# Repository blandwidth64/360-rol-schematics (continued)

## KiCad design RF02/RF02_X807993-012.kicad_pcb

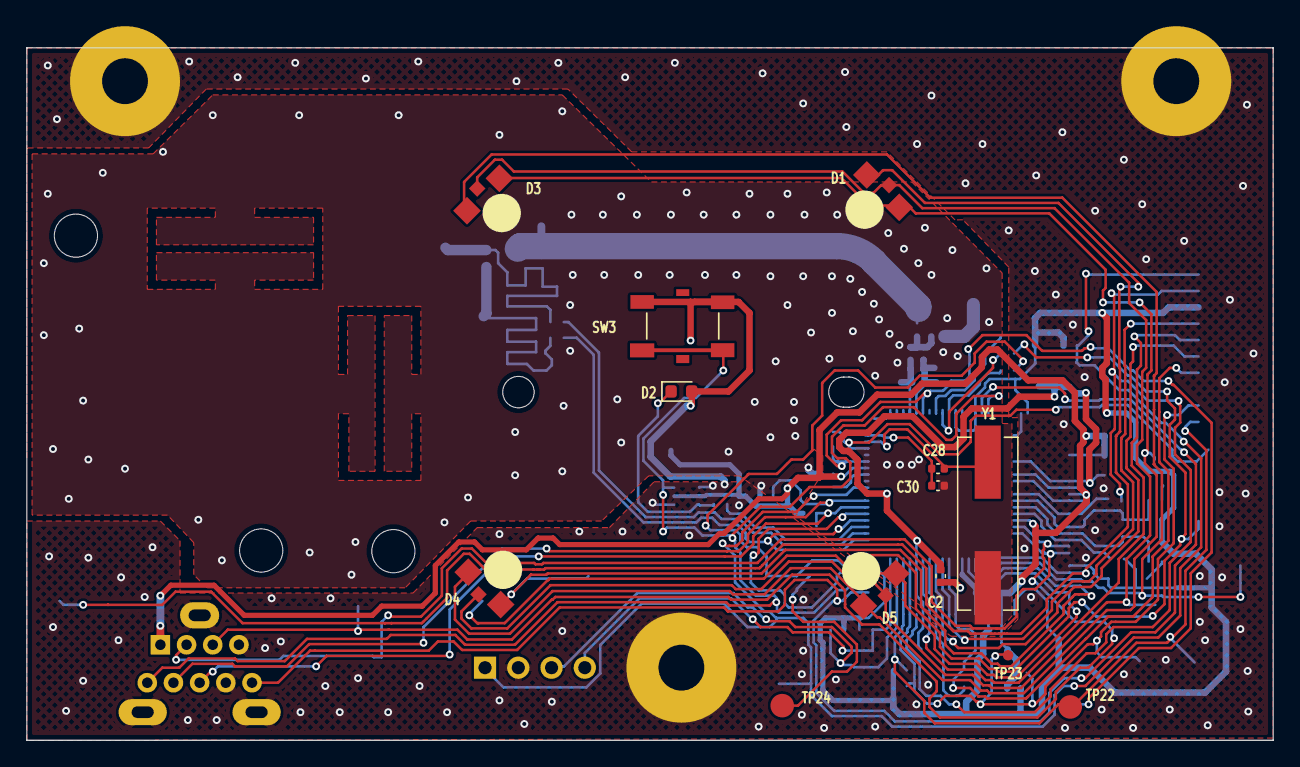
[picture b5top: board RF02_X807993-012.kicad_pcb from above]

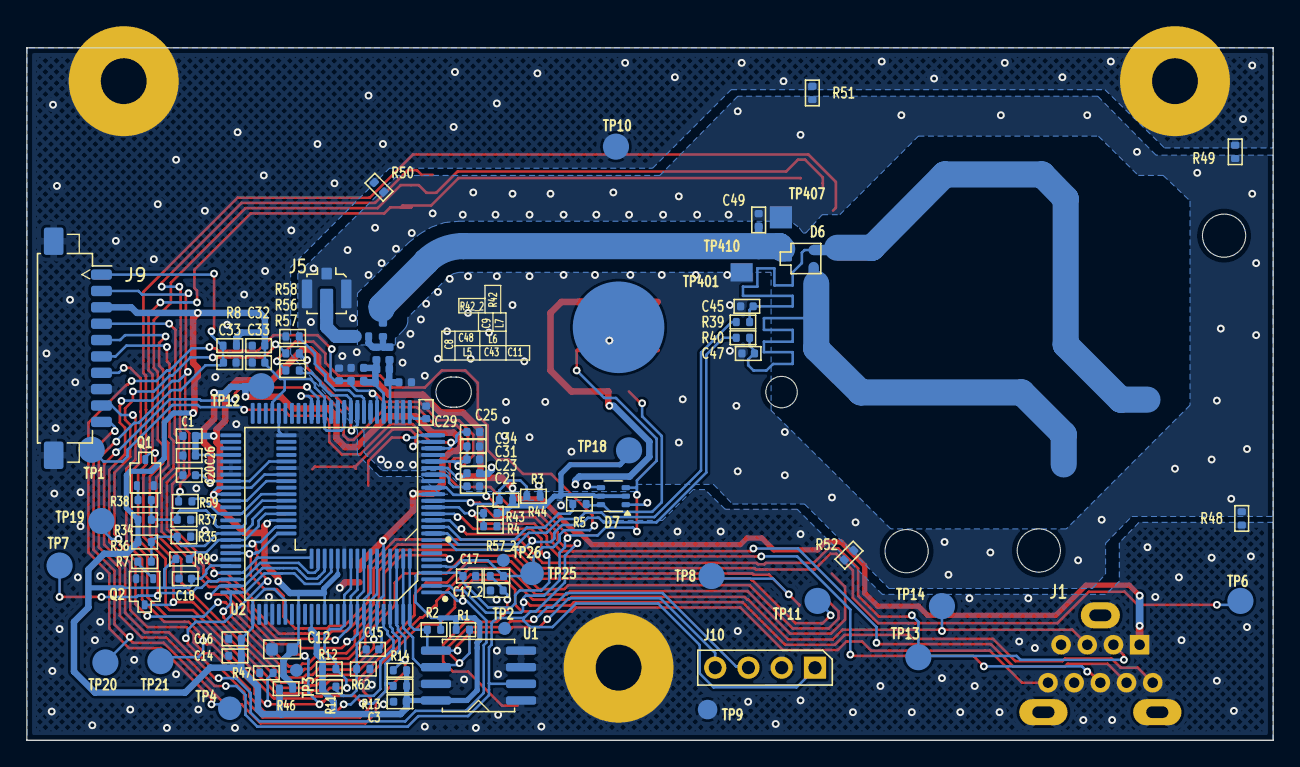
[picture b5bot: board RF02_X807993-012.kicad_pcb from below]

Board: 2 copper layers, 95.2 x 52.9 mm, 115 parts (100 on the bottom side), 58 nets.

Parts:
A1: Argon_ANT
C1, C3, C8, C14, C15, C16, C17, C17_2, C18, C20, C21, C23, C25, C26, C29, C31, C32, C33, C33#2, C34: 0.1 UF; C_0402_1005Metric
C2, C9, C28, C30: C_0402_1005Metric
C11, C43, C48: ~2 PF; C_0402_1005Metric
C12: 0.33 UF; C_0603_1608Metric
C45, C47: ~6.2 PF; C_0402_1005Metric
C49: NC; C_0402_1005Metric
D1, D3, D4, D5: LED_LiteOn_LTST-S326
D2: LED_0603_1608Metric
D6: SOT-323_SC-70
D7: SOT-363_SC-70-6
J1: Argon_Conn
J5: U.FL_Molex_MCRF_73412-0110_Vertical
J9: Molex_PicoBlade_53261-1071_1x10-1MP_P1.25mm_Horiz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; Molex_PicoBlade_53261-1071_1x10-1MP_P1.25mm_Horizontal
J10: PinHeader_1x04_P2.54mm_Vertical
L5, L6, L7: L_0402_1005Metric
Q1, Q2: SOT-323_SC-70
R1, R2: 1.5 KOHM; R_0402_1005Metric
R3, R4, R9, R11, R34, R36, R43, R44, R47, R48, R49, R50, R51, R52, R57_2: NC; R_0402_1005Metric
R5: 220 OHM; R_0402_1005Metric
R7, R38: 1 KOHM; R_0402_1005Metric
R8, R42, R42_2: 47 KOHM; R_0402_1005Metric
R12, R13, R14, R35, R37, R46, R62: 10 KOHM; R_0402_1005Metric
R39, R40: 390 OHM; R_0402_1005Metric
R56, R57, R58, R59: 0 OHM; R_0402_1005Metric
SW3: SW_Push_1P1T_XKB_TS-1187A
TP1, TP2, TP3, TP4, TP6, TP7, TP8, TP9, TP10, TP11, TP12, TP13, TP14, TP18, TP19, TP20, TP21, TP22, TP23, TP24, TP25, TP26, TP410: TestPoint_Pad_D2.0mm
TP35: TestPoint_Pad_D3.0mm
TP401, TP407: TestPoint_Pad_2.0x2.0mm
U1: SOIC-8_5.3x5.3mm_P1.27mm
U2: LQFP-64_10x10mm_P0.5mm
U2_2: LQFP-100_14x14mm_P0.5mm
Y1: Crystal_SMD_HC49-SD

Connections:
ANT_01: A1.1, C45.1, D6.2, R39.2
ANT_01_MATCHING: R39.1, U2.1, U2_2.10
ANT_02: A1.2, C47.1, D6.1, R40.2
ANT_02_MATCHING: R40.1, U2.3, U2_2.9, U2_2.12
ANT_C: C9.1, C43.1, C48.1, L5.2, L6.1, U2.21, U2_2.30
ANT_COAX: J5.1, R42_2.2
ANT_L: C11.1, C43.2, L6.2, L7.1, U2.20, U2_2.29
ANT_MAIN: C49.1, D6.3, R42.1, TP410.1
ANT_R: C9.2, L7.2, R42.2, R42_2.1
C_CLK: J1.C_CLK, R4.1, R43.2, U2.5, U2_2.14
C_DATA: J1.6, R3.1, R44.2, U2.6, U2_2.15
C_NTX: J1.9, U2.31, U2_2.1, U2_2.40
GND: C1.2, C2.1, C3.2, C12.2, C14.2, C15.2, C16.2, C17.2, C17_2.2, C18.2, C20.2, C23.2, C26.2, C32.2, C33.2, C33#2.2, D2.2, D7.1, D7.4, J1.4, J1.8, J1.MP, J9.8, J9.MP, J10.2, Q1.2, Q2.2, R3.2, R4.2, R35.2, R37.2, R47.2, R48.2, R49.2, R50.2, R51.2, R52.2, R58.2, R62.2, SW3.2, TP9.1, TP10.1, TP35.1, U1.1, U1.3, U1.4, U1.7, U2.9, U2.33, U2.38, U2.54, U2_2.18, U2_2.46, U2_2.55, U2_2.56, U2_2.57, U2_2.70, U2_2.78, U2_2.79
GND_0R: R58.1, U2.24, U2_2.33
HEADER_02: J9.2, R59.2, U2_2.96
HEADER_02_0R: R59.1, U2.42, U2_2.63
HEADER_04: J9.4, U2.56, U2_2.91
HEADER_05: J9.5, U2.59, U2_2.94
HEADER_06: J9.6, U2.57, U2_2.92
HEADER_07: J9.7, R12.2, U2.55, U2_2.90
I2C_EN: C33#2.1, J9.1, J10.1, R8.2, U1.2, U2.8, U2_2.17
I2C_SCL: J10.3, R1.1, U1.6, U2.63, U2_2.99
I2C_SDA: J10.4, R2.1, U1.5, U2.64, U2_2.100
LED_GRN_CATHODE: D1.2, D3.2, D4.2, D5.2, Q2.3
LED_GRN_CATHODE_EN: Q2.1, R7.2
LED_GRN_CATHODE_EN_R: R7.1, R35.1, R36.1, U2.44, U2_2.66
LED_PL1_EN: D1.3, TP6.1, U2.49, U2_2.72
LED_PL2_EN: D3.3, TP7.1, U2.50, U2_2.73
LED_PL3_EN: D4.3, TP8.1, U2.51, U2_2.74
LED_PL4_EN: D5.3, TP11.1, U2.52, U2_2.75
LED_PWR_EN: D2.1, D7.6, R5.1
LED_PWR_EN_R: R5.2, U2.2, U2_2.11
LED_RED_CATHODE: D1.1, D3.1, D4.1, D5.1, Q1.3
LED_RED_CATHODE_EN: Q1.1, R38.2
LED_RED_CATHODE_EN_R: R34.1, R37.1, R38.1, U2.43, U2_2.65
NC: TP2.1, TP3.1, TP26.1, U2.23, U2.28, U2.29, U2.34, U2.35, U2.36, U2.41, U2_2.3, U2_2.7, U2_2.8, U2_2.32, U2_2.37, U2_2.38, U2_2.42, U2_2.43, U2_2.44, U2_2.45, U2_2.48, U2_2.49, U2_2.50, U2_2.51, U2_2.52, U2_2.53, U2_2.62, U2_2.64, U2_2.77, U2_2.80, U2_2.82, U2_2.84, U2_2.86, U2_2.88, U2_2.89
PWRSW_N: D7.3, J1.5, SW3.1, U2.32, U2_2.2, U2_2.41
S2B_01: R56.1, U2.25, U2_2.34
S2B_01_0R: R56.2, TP19.1, U2_2.6
S2B_02: R57.1, U2.26, U2_2.35
S2B_02_0R: R57.2, R57_2.1, TP25.1, U2_2.5
S2B_02_decouple: C17_2.1, R57_2.2, TP24.1
SMD_XTAL: C28.2, U2.15, U2_2.24, Y1.1
SMD_XTAL_C: C28.1, C30.1, U2.16, U2_2.25
S_GND: C8.2, C11.2, C21.2, C25.2, C29.2, C30.2, C31.2, C34.2, C45.2, C47.2, C48.2, C49.2, J5.2, R48.1, R49.1, R50.1, R51.1, R52.1, TP401.1, TP407.1, U2.13, U2.18, U2.19, U2_2.22, U2_2.27, U2_2.28, Y1.2
UART_RX: J9.9, R13.2, R47.1, TP21.1, TP23.1, U2.61, U2_2.97
UART_TX: J9.10, R14.2, TP20.1, TP22.1, U2.62, U2_2.98
USB_DN: J1.2, TP13.1, U2.48, U2_2.69
USB_DP: J1.3, TP14.1, U2.47, U2_2.68
V_3P3: C1.1, C12.1, C23.1, C26.1, D7.2, D7.5, J1.1, R43.1, R44.1, R46.2, TP18.1, U2.11, U2.39, U2.40, U2.46, U2.53, U2_2.20, U2_2.54, U2_2.59, U2_2.60, U2_2.61, U2_2.83, U2_2.87
V_3P3_ISO: C3.1, C14.1, C16.1, C17.1, C18.1, C32.1, C33.1, J9.3, R1.2, R2.2, R8.1, R9.2, R11.1, R12.1, R13.1, R14.1, R34.2, R36.2, R46.1, U1.8, U2.4, U2.27, U2.30, U2_2.4, U2_2.13, U2_2.36, U2_2.39, U2_2.47, U2_2.71, U2_2.76, U2_2.81, U2_2.85
V_3P3_ISO_NC: R9.1, U2.45, U2_2.67
V_3P3_NC: R11.2, R62.1, U2.58, U2_2.93
decouple_1: C2.2, C15.1, C20.1, TP12.1, U2.7, U2.37, U2.60, U2_2.16, U2_2.58, U2_2.95
decouple_2: C25.1, TP1.1, U2.14, U2_2.23
decouple_3: C29.1, U2.17, U2_2.26
decouple_4: C8.1, C31.1, C34.1, L5.1, TP4.1, U2.12, U2.22, U2_2.21, U2_2.31
decouple_5: C21.1, U2.10, U2_2.19

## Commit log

2025-02-21 Update README.md
    i mean... yea
2025-04-09 Rename 01 top.png to 01 top.png
2025-04-09 Rename 02 top strip.png to 02 top strip.png
2025-04-09 Rename 03 bottom.png to 03 bottom.png
2025-04-09 Rename 04 bottom strip.png to 04 bottom strip.png
